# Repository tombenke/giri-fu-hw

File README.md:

giri-fu-hw v2.0
===============

Hardware module of the giri-fu functional unit, that is a simple relay board, with its own MCU.

It is a proof of concept for a tiny autonomous device, that is able to control 24 VAC magnetic valves in real circumstances:

- wet and dirty environment,
- wide range of temperature,
- mechanical stress.

The [functional block diagram of the unit](docs/images/giri-fu-hw_fbd.png) below demonstrates how to connect it into its environment:

The v1.0.x version is just documenting [the early prototype](docs/images/prototype.jpg?raw=true "giri-fu-hw prototype"),
that was made on a raster panel. (Note: The PCB design differs from the raster panel version).

The PCB layout was intentionally designed to be very simple, in order to make it easy to reproduce with DIY technologies.

The top layer can be substituted with, straight jumper wires, so it is enought to make a one-sided panel, with the bottom layout.

The firmware implementation can be found in the [giri-fu firmware repository](https://github.com/tombenke/giri-fu).

## Features

- Standalone MCU (ATMega328P, 16MHz)
- High-voltage, high-current darlington transistor array (ULN2003A)
- 6 relays to switch 24V AC current, for magnetic valves (RSY-5)
- 12V AC input for Power supply
- RS-485 serial communication port

Dimensions: 3.6 x 2.15 x 0.5 inch

Boxing: The minimum required internal size of box: 4.75 x 3 x 1.5 inch

Mounting: N.A.

Inputs:

- 12V AC, min: ? A (TBD.)
- 24V AC, min: ? A (TBD.)

Outputs (6x):

- Carry current: 2 A
- Max. operating voltage: 125 VAC, 60 VDC
- Max. operating current: 1 A
- Max. switching capacity: 62.50 VA, 30W
- Min. permissible load: 1 mA, 5 VDC

## Artifacts

The `src` folder holds the EAGLE files:

- `src/giri-fu-hw.sch`
- `src/giri-fu-hw.brd`

The `dist` folder contains the final products for manufacturing:

- [The schematic diagram](dist/giri-fu-hw_sch.pdf)
- [The PCB layout](dist/giri-fu-hw_brd.pdf)
- [PCB top layer (to print)](dist/giri-fu-hw_top.pdf)
- [PCB bottom layer (to print)](dist/giri-fu-hw_bottom.pdf)

## References

- [giri-fu firmware](https://github.com/tombenke/giri-fu)
- [ATMega328P datasheet](http://www.atmel.com/Images/Atmel-42735-8-bit-AVR-Microcontroller-ATmega328-328P_datasheet.pdf)
- [Rayex RSY-5 relay datasheet](docs/datasheets/RSY-5G5V1K5V1_EN.pdf)
- [ULN2003A datsheet](https://www.sparkfun.com/datasheets/IC/ULN2003A.pdf)
- [Making of PCBs at home, DIY using inexpenive materials](https://www.youtube.com/watch?v=mv7Y0A9YeUc)
- [Heatless (cold) Toner Transfer (for PCB)](https://www.youtube.com/watch?v=HBIxvwZ_0og)
- [yEd - GraphML Editor, used for Functional Block Diagram creation](http://www.yworks.com/products/yed)
- [EAGLE PCB Design tool](https://cadsoft.io/)

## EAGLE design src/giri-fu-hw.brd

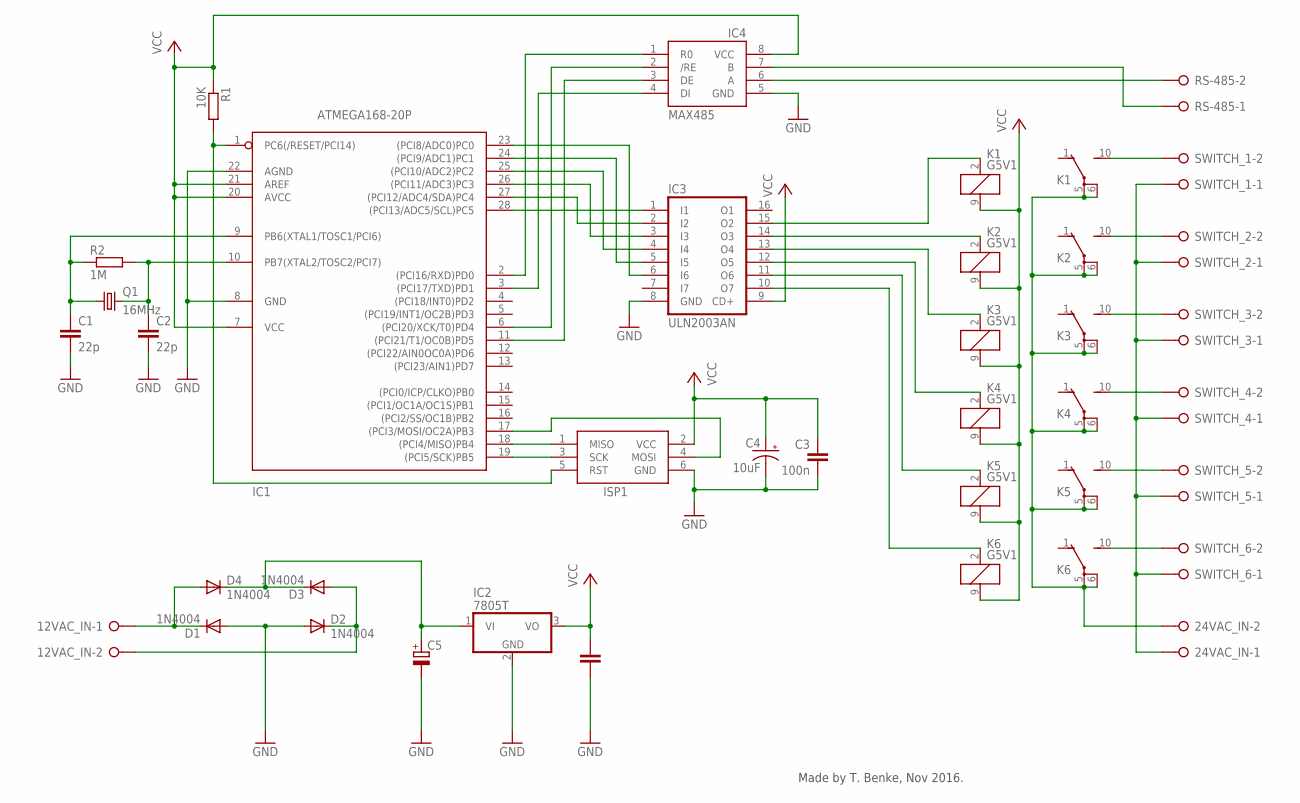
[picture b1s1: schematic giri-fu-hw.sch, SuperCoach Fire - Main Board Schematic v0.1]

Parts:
12VAC_IN, 24VAC_IN: W237-02P; W237-132
C1, C2: 22p; C025-025X050
C3: 100n; C025-025X050
C4: 10uF; E2-5
C5: CPOL-EUE35-12AXIAL; E35-12
D1, D2, D3, D4: 1N4004; DO41-10
IC1: ATMEGA168-20P; DIL28-3
IC2: 7805T; TO220H
IC3: ULN2003AN; DIL16
IC4: MAX485; DIL08
ISP1: AVRISP-6; AVRISP
K1, K2, K3, K4, K5, K6: G5V1
Q1: 16MHz; HC49U-V
R1: 10K; 0207/10
R2: 1M; 0207/10
RS-485: W237-02P; W237-132
SWITCH_1, SWITCH_2, SWITCH_3, SWITCH_4, SWITCH_5, SWITCH_6: W237-02P; W237-132

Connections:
GND: C1.2, C2.2, C3.2, C4.-, C5.-, D1.A, D2.A, IC1.8 (GND), IC1.22 (AGND), IC2.2 (GND), IC3.8 (GND), IC4.5 (GND), ISP1.6 (GND)
unnamed: IC1.23 ((PCI8/ADC0)PC0), IC3.6 (I6)
unnamed: IC1.24 ((PCI9/ADC1)PC1), IC3.5 (I5)
unnamed: 24VAC_IN.2, K1.5, K1.6, K2.5, K2.6, K3.5, K3.6, K4.5, K4.6, K5.5, K5.6, K6.5, K6.6
unnamed: IC1.25 ((PCI10/ADC2)PC2), IC3.4 (I4)
unnamed: IC1.28 ((PCI13/ADC5/SCL)PC5), IC3.1 (I1)
unnamed: IC1.26 ((PCI11/ADC3)PC3), IC3.3 (I3)
unnamed: IC1.27 ((PCI12/ADC4/SDA)PC4), IC3.2 (I2)
unnamed: C3.1, C4.+, IC1.7 (VCC), IC1.20 (AVCC), IC1.21 (AREF), IC2.3 (VO), IC3.9 (CD+), IC4.8 (VCC), ISP1.2 (VCC), K1.9 (2), K2.9 (2), K3.9 (2), K4.9 (2), K5.9 (2), K6.9 (2), R1.1
unnamed: IC3.10 (O7), K6.2 (1)
unnamed: IC3.11 (O6), K5.2 (1)
unnamed: IC1.19 ((PCI5/SCK)PB5), ISP1.3 (SCK)
unnamed: IC1.17 ((PCI3/MOSI/OC2A)PB3), ISP1.4 (MOSI)
unnamed: IC1.1 (PC6(/RESET/PCI14)), ISP1.5 (RST), R1.2
unnamed: C1.1, IC1.9 (PB6(XTAL1/TOSC1/PCI6)), Q1.1, R2.1
unnamed: C2.1, IC1.10 (PB7(XTAL2/TOSC2/PCI7)), Q1.2, R2.2
unnamed: IC1.18 ((PCI4/MISO)PB4), ISP1.1 (MISO)
unnamed: IC3.12 (O5), K4.2 (1)
unnamed: IC3.13 (O4), K3.2 (1)
unnamed: IC3.14 (O3), K2.2 (1)
unnamed: IC3.15 (O2), K1.2 (1)
unnamed: C5.+, D3.C, D4.C, IC2.1 (VI)
unnamed: 12VAC_IN.1, D1.C, D4.A
unnamed: 12VAC_IN.2, D2.C, D3.A
unnamed: IC4.6 (A), RS-485.2
unnamed: IC4.7 (B), RS-485.1
unnamed: IC1.2 ((PCI16/RXD)PD0), IC4.1 (R0)
unnamed: IC1.3 ((PCI17/TXD)PD1), IC4.4 (DI)
unnamed: K1.10 (S), SWITCH_1.2
unnamed: K2.10 (S), SWITCH_2.2
unnamed: K3.10 (S), SWITCH_3.2
unnamed: K4.10 (S), SWITCH_4.2
unnamed: K5.10 (S), SWITCH_5.2
unnamed: K6.10 (S), SWITCH_6.2
unnamed: 24VAC_IN.1, SWITCH_1.1, SWITCH_2.1, SWITCH_3.1, SWITCH_4.1, SWITCH_5.1, SWITCH_6.1
unnamed: IC1.6 ((PCI20/XCK/T0)PD4), IC4.2 (/RE)
unnamed: IC1.11 ((PCI21/T1/OC0B)PD5), IC4.3 (DE)

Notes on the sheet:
Made by T. Benke, Nov 2016.

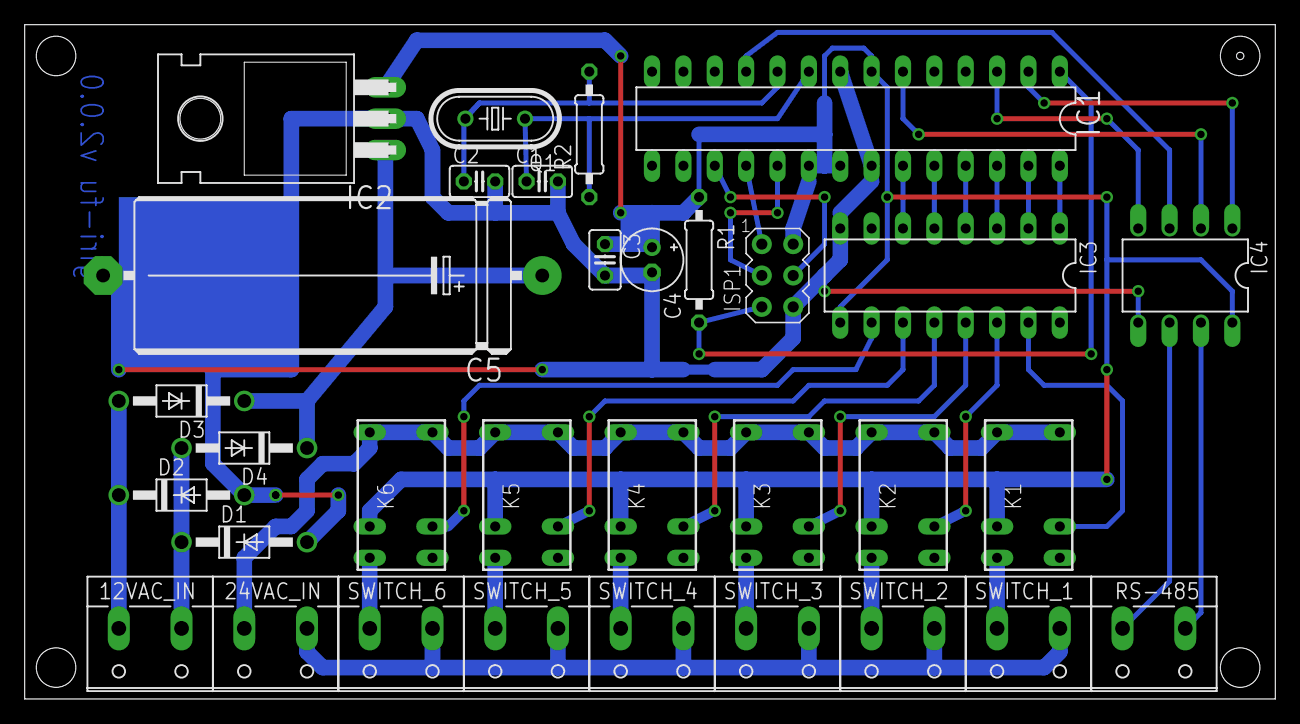
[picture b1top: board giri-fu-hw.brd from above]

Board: 2 copper layers, 101.3 x 54.6 mm, 32 parts (0 on the bottom side), 37 nets.

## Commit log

2016-11-07 Initial import
2016-11-12 Add Schematics Add PCB board design Add top and bottom prints for manual PCB manufacturing Add partlist Add photo on the prototype board Add datasheet to the RYS-5 relay
2016-11-12 Rename prototype image Write README content
2016-11-12 Add extension to prototype link
2016-11-12 Add reference links to README
2016-11-12 Add some text to the about section of README
2016-11-12 fix typo in .gitignore rename and replace schema and board files in README Add a new board pdf
2016-11-12 Rename inputs and outputs Regenerate dist artifacts
2016-11-12 Add functional block diagram
2016-11-12 Add links to EAGLE and yED Add FBD text to README
2016-11-12 Add LICENCE file
2016-11-13 Add version tag to the title of README
2016-11-24 Add link about PCB making to README
2017-03-15 Change the relay driver endpoint from ground to vcc
2017-06-09 Add RS485 adapter
2017-06-09 Fix the version number in README
